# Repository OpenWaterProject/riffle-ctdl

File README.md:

# riffle-ctdl
breakout board -- conductivity - temp - depth - light

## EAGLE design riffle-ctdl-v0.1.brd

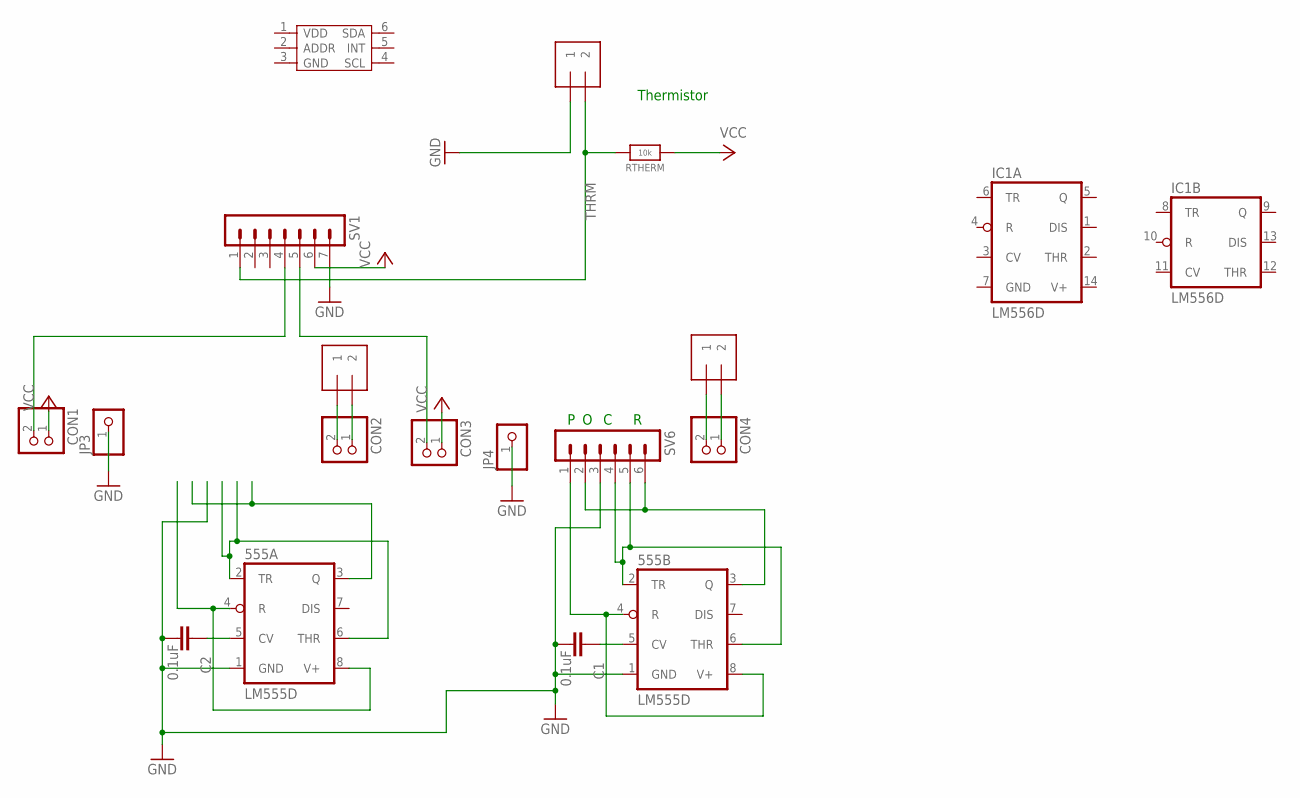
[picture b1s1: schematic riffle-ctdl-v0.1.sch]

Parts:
555A, 555B: LM555D; SO08
C1, C2: 0.1uF; 0603-CAP
CON1, CON2, CON3, CON4: PINHD-1X2; 1X02
IC1: LM556D; SO14
IN1, IN2: 1X2-3.5MM
JP3, JP4: PINHD-1X1; 1X01
RTHERM: 10k; 0603-NO
SV1: MA07-1
SV6: MA06-1
THRM: 1X2-3.5MM
U1: TSL2561T; TMB-6

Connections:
AOUT: 555A.3 (Q)
AOUT1: 555B.3 (Q), SV6.2, SV6.6
GND: 555A.1 (GND), 555B.1 (GND), C1.1, C2.1, IC1.7 (GND), JP3.1, JP4.1, SV1.7, SV6.3, THRM.1
unnamed: 555B.2 (TR), 555B.6 (THR), SV6.4, SV6.5
unnamed: 555B.5 (CV), C1.2
unnamed: CON2.2, IN1.1
unnamed: 555A.2 (TR), 555A.6 (THR)
unnamed: 555A.5 (CV), C2.2
unnamed: CON2.1, IN1.2
unnamed: CON4.2, IN2.1
unnamed: CON4.1, IN2.2
unnamed: CON1.2, SV1.4
unnamed: CON3.2, SV1.5
THRM: RTHERM.2, SV1.1, THRM.2
V+: IC1.14 (V+)
VAIN: 555A.4 (R), 555A.8 (V+)
VAIN1: 555B.4 (R), 555B.8 (V+), SV6.1
VCC: CON1.1, CON3.1, RTHERM.1, SV1.6

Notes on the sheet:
Thermistor

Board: 2 copper layers, 18 parts (0 on the bottom side), 16 nets, no tracks yet.

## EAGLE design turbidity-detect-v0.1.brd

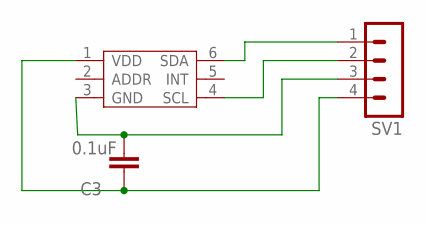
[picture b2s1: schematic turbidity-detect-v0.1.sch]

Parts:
C3: 0.1uF; 0603-CAP
SV1: MA04-1
U1: TSL2561T; TMB-6

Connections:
GND: C3.1, SV1.3, U1.3 (GND)
unnamed: SV1.1, U1.6 (SDA)
unnamed: SV1.2, U1.4 (SCL)
VDD: C3.2, SV1.4, U1.1 (VDD)

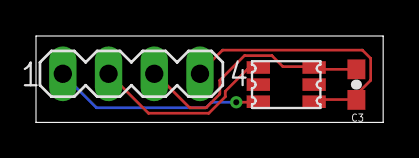
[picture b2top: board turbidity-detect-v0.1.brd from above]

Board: 2 copper layers, 19.3 x 4.8 mm, 3 parts (0 on the bottom side), 4 nets.

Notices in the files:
parts and their libraries:
microbuilder: This work is placed in the public domain, and may be freely used for commercial and non-commercial work with the following conditions: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
